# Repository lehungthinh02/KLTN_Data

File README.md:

# Bảng dữ liệu thiết kế

Thông tin chi tiết về các module được sử dụng trong thiết kế:

## Module (NB-IOT ME310G1)

| Thuộc tính    | Giá trị         |
|---------------|-----------------|
| Điện áp nguồn | 3.8V            |
| Dòng điện     | 700 mA          |
| Giao tiếp     | UART, SPI, LTE  |

## MCU (PIC32MM0256GPM064)

| Thuộc tính    | Giá trị                |
|---------------|------------------------|
| Điện áp nguồn | 2.0V đến 3.6V          |
| Dòng điện     | 0.65 μA đến 5 μA       |
| Giao tiếp     | SPI, I2C, UART, USB-OTG|

# Nguồn tài liệu

- [File 3D và danh sách bom](https://www.thingiverse.com/thing:6439737)

# Sơ đồ thiết kế

Mô tả quy trình hoạt động:

# Case of Board

Mô tả về case bảo vệ board:

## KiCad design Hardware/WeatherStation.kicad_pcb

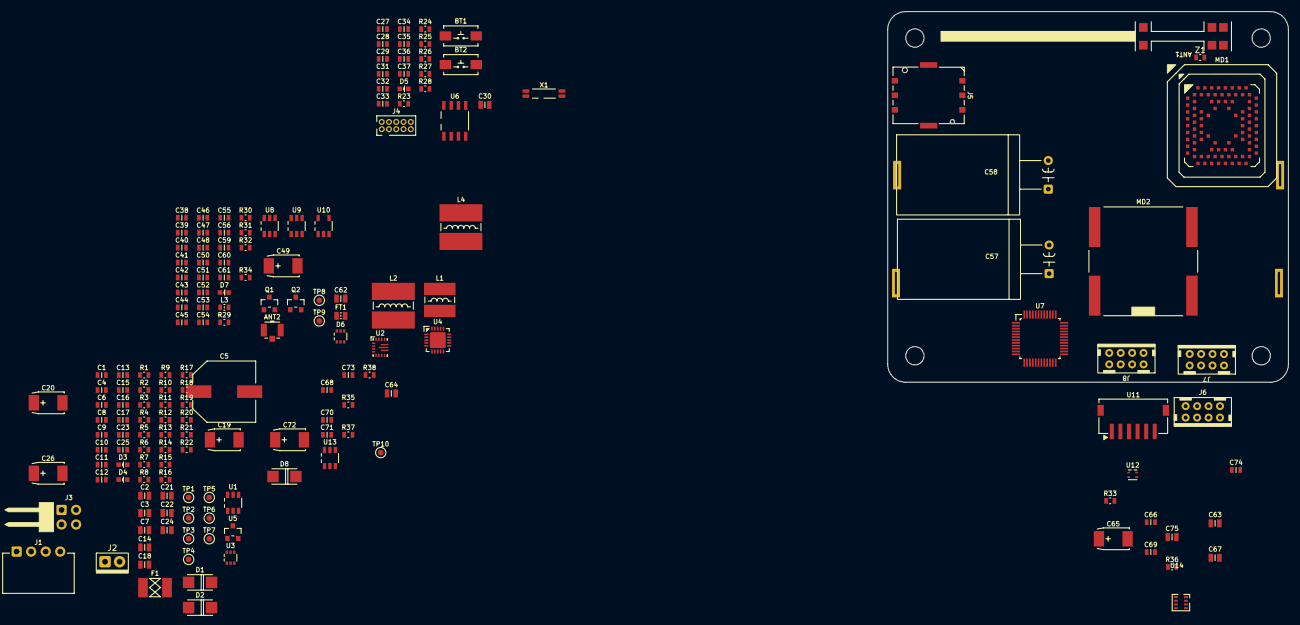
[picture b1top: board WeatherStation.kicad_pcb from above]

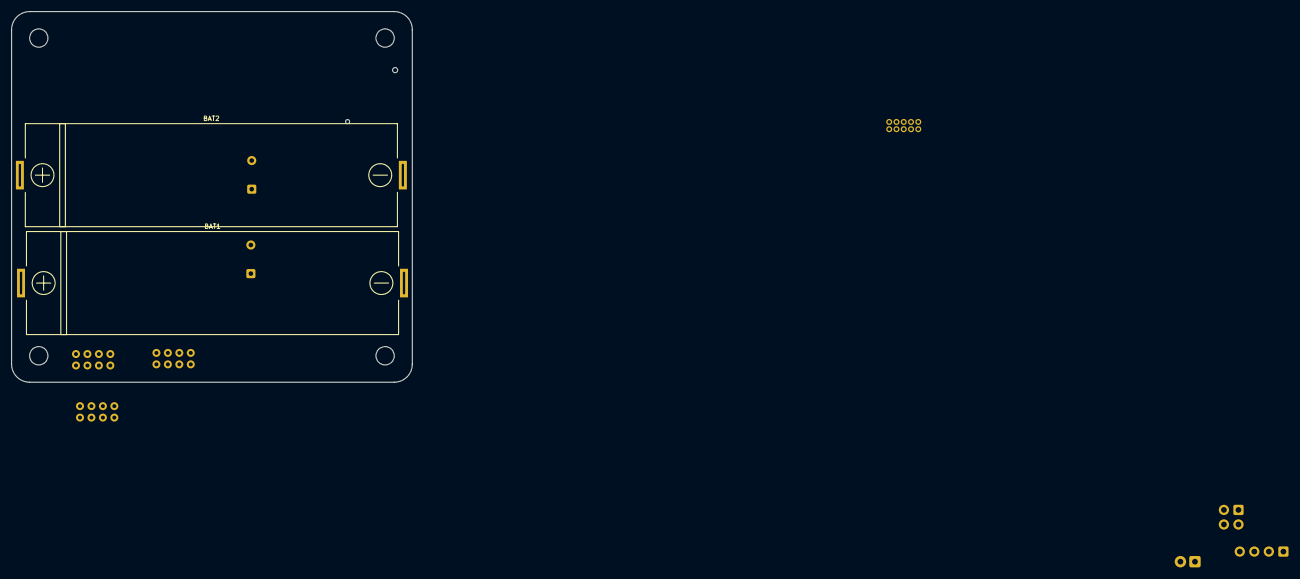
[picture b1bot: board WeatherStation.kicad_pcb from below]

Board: 2 copper layers, 70.0 x 64.7 mm, 171 parts (2 on the bottom side), 92 nets, no tracks yet.

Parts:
ANT1: 0.9-1.8GHz; AH3G.303
ANT2: UFL; U.FL
BAT1, BAT2: 3.7V/1.8Ah; BAT18650-PCBPAD
BT1: RESET; SW_SMD2_6.0x3.5
BT2: APP; SW_SMD2_6.0x3.5
C1, C6, C12, C16, C17, C25, C27, C34, C41, C42, C46, C47, C51, C61, C66, C70, C74: 100nF; CAP0603
C2, C3, C7, C14, C18, C21, C22, C24, C30, C62, C63, C64, C67, C75: 10uF; CAP0805
C4, C9, C10, C11, C13, C15, C23, C68, C69: 100pF; CAP0603
C5: 470uF; CAP_ELEC-10.3x10.3-DIA10
C8, C31, C36, C44, C50, C55, C60: 2.2uF; CAP0603
C19, C20, C26, C49, C65, C72: 220uF; CAP2312-6032
C28, C29: 8.2pF; CAP0603
C32, C33, C35, C37, C38, C39, C40, C43, C45, C48, C52, C53, C54, C56, C59, C71, C73: 22pF; CAP0603
C57, C58: 10F/2.7V; SCAP1320
D1, D2, D8: 2A/0.5VF; DO-214AC
D3: LOW BAT; LED0603
D4: CHARGE; LED0603
D5: APP; LED0603
D6: TVS-5CH; SOT363
D7: NB; LED0603
F1: 750mA/6.3V; FUSE1812
FT1: 100R@100MHz; IND0805
J1: USB; HDM-1x4x2.54-TH-RA
J2: SOLAR; PAD02_2.54TH
J3: PWR MONITOR; DIL04_2.54_MTHRA
J4: RPDBG; DIL10_1.27_MTH
J5: NANOSIM; SIM8051-6-0-14-01-A_GCT
J6, J7, J8: DIL08; HDM-2x4x2.0-TH-RA
L1: 2.2uH/3A; IND5852
L2, L4: 10uH/3A; IND7870
L3: 47nH; IND0603
MD1: NB-IoT MODULE; xE310
MD2: GPS ACTIVE ANTENNA; 1575R-A
Q1, Q2: MFET N; SOT23
R1, R6, R10, R13, R14, R15, R26, R28, R31, R32, R36: 1K; RES0603
R2, R5, R23, R24: 5.1K, 1%; RES0603
R3, R4, R9, R12, R16, R18, R20, R22, R25, R30, R35: 10K, 1%; RES0603
R7, R34: 75K, 1%; RES0603
R8: 36K, 1%; RES0603
R11: 53.6K, 1%; RES0603
R17: 100K, 1%; RES0603
R19: 680K, 1%; RES0603
R21, R27, R29: 0R; RES0603
R33: 150R; RES0603
R37, R38: 150K, 1%; RES0603
TP1: VUSB; TP1MM
TP2: VNB; TP1MM
TP3: 5V; TP1MM
TP4: 3V3; TP1MM
TP5: VBAT; TP1MM
TP6: GND; TP1MM
TP7: VDD; TP1MM
TP8: 1V8; TP1MM
TP9: VLNA; TP1MM
TP10: VBOOST; TP1MM
U1: BUCK 5V; SOT-23-6_MCHP
U2: BUCK-BOOST 3.8V; PowerVQFN15_TI
U3: IDEAL DIODE; SOT363
U4: MCP73871; VQFN20-4x4_MCHP
U5: MCP1700; SOT23
U6: SPI Memory; SOIC8_3.9_MCHP
U7: PIC32MM MCU; TQFP48-7x7_MCHP
U8, U9: LEVEL SHIFT 1-CH; SOT-23-6_MCHP
U10: LDO 3.3V/300mA; SOT-23-5_MCHP
U11: DUST SENSOR CONNECTOR; HDM-6x1.5-SMD-RA
U12: HUMI & TEMP; SHT4x
U13: BOOST 5V; SOT-23-6_MCHP
U14: DPS368
X1: 32.768kHz; SMD4-7015
Z1: 0R; RES0603

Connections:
+1V8: C46.1, C47.1, C51.1, MD1.N16 (~ONOFF/~WAKE), TP8.1, U8.6 (VCCB), U9.1 (VCCA), U9.5 (DIR)
+3.3V: C24.1, C27.1, C31.2, C33.1, C34.1, C36.1, C37.1, D3.A, J4.4 (VDD), J7.1, J8.1, R22.1, R23.2, R24.2, R25.1, R37.1, R38.1, TP4.1, U5.2 (VOUT), U6.3 (~WP), U6.7 (~HOLD), U6.8 (VDD), U7.11 (VUSB3V3), U7.18 (AVDD/VDD), U7.30 (VDD), U7.43 (VDD)
+5V: C11.1, C12.1, C14.1, C17.1, C20.+, D2.K, D4.A, R11.1, TP3.1, U3.6 (VOUT), U4.2 (VPCC), U4.4 (PROG2), U4.17 (CE), U4.18 (IN), U4.19 (IN)
/MCU/DBG_RXD: J4.3 (DBG_RX), U7.26 (TDI/AN11/C1INA/RP9/SCL2/OCM2F/RB3)
/MCU/DBG_TXD: J4.1 (DBG_TXD), U7.25 (AN4/C1INB/RP8/SDA2/OCM2E/RB2)
/MCU/NB_DN: J4.7 (USB_DM), MD1.V18 (USB_D-)
/MCU/NB_DP: J4.5 (USB_DP), MD1.U19 (USB_D+)
/MCU/NB_VBUS: J4.9 (USB_VBUS), R29.1
/MCU/PGC: J4.10 (PGC), U7.24 (PGEC1/AN3/C1INC/C2INA/RP7/OCM2D/RB1)
/MCU/PGD: J4.8 (PGD/UPDI), U7.23 (PGED1/AN2/C1IND/C2INB/C3INC/RP6/RB0)
/MCU/SCL: J7.7, J8.2, R24.1
/MCU/SDA: J7.8, J8.3, R23.1
/MCU/SOSCI: C28.1, U7.35 (SOSCI/AN7/RP10/OCM3C/RB4), X1.1 (X1)
/MCU/SOSCO: C29.1, U7.36 (SOSCO/SCLKI/RP5/PWRLCLK/OCM3D/RA4), X1.4 (X2)
/MCU/USB_DN: J1.3, U7.9 (D-/RB10)
/MCU/USB_DP: J1.2, U7.10 (D+/RB11)
/MCU/V5V_SEN: C15.1, R13.1
/MCU/VBAT_SEN: C23.1, R19.2, R20.1
/MCU/VBUS_SEN: C9.1, R6.1, U7.46 (VBUS/RB6)
/MCU/VNB_EN: R27.1, U2.1 (PS/SYNC), U2.14 (EN)
/MCU/VNB_SEN: C13.1, R10.1
/MCU/VSOLAR_SEN: C4.1, R1.1
/MCU/~BT_APP: BT2.1, C35.1, R25.2
/MCU/~MCLR: BT1.1, C32.1, J4.2 (~RESET), R22.2, U7.19 (~MCLR)
/MCU/~RNF_PULSE: C73.1, J8.8, R38.2
/MCU/~VBAT_LOW: R14.2, U4.8 (STAT1/~LDB)
/MCU/~WSP_PULSE: C71.1, J8.6, R37.2
/NB MODULE/GPS_LNA_ENA: MD1.H18 (GNSS_LNA_EN), U10.3 (EN)
/NB MODULE/RXD0: MD1.AA15 (RXD0), U9.3 (A)
/NB MODULE/SIM_CLK: C40.1, D6.3 (CH2), J5.C3 (CLK), MD1.L1 (SIM_CLK)
/NB MODULE/SIM_DAT: C38.1, D6.1 (CH1), J5.C7 (I/O), MD1.N1 (SIM_DAT)
/NB MODULE/SIM_RST: C43.1, D6.4 (CH3), J5.C2 (RST), MD1.M2 (SIM_RST)
/NB MODULE/SIM_VCC: C44.2, D6.5 (CH4), J5.C1 (VCC), MD1.P2 (SIM_VCC)
/NB MODULE/TXD0: MD1.Y16 (TXD0), R31.1
/SENSORS/SCL1: J6.7, U12.2 (SCL), U14.4 (SCK/SCL)
/SENSORS/SDA1: J6.8, U12.1 (SDA), U14.3 (SDI/SDA)
/SENSORS/VOUT: C69.1, J6.5, R36.1
/SENSORS/~LED_EN: J6.6, U11.3 (~LED_EN)
GND: ANT1.1 (GND), ANT1.3 (GND), ANT2.2 (GND), ANT2.3 (GND), BAT1.-, BAT2.-, BT1.2, BT2.2, C1.2, C2.2, C3.2, C4.2, C5.-, C6.2, C7.2, C9.2, C12.2, C13.2, C14.2, C15.2, C16.2, C17.2, C18.2, C19.-, C20.-, C21.2, C22.2, C23.2, C24.2, C25.2, C26.-, C27.2, C28.2, C29.2, C30.2, C31.1, C32.2, C33.2, C34.2, C35.2, C36.2, C37.2, C38.2, C39.2, C40.2, C41.2, C42.2, C43.2, C44.1, C45.2, C46.2, C47.2, C48.2, C49.-, C50.1, C51.2, C52.2, C54.2, C55.1, C56.2, C58.-, C59.2, C60.1, C61.2, C62.1, C64.2, C70.2, C71.2, C72.-, C73.2, D5.K, D6.2 (GND), J1.1, J2.2, J3.3, J3.4, J4.6 (GND), J5.C5 (GND), J5.S1 (SHIELD), J5.S2 (SHIELD), J7.3, J7.4, J8.4, J8.5, J8.7, MD1.A3 (GND), MD1.A7 (GND), MD1.A9 (GND), MD1.A13 (GND), MD1.A17 (GND), MD1.B4 (GND), MD1.B6 (GND), MD1.B10 (GND), MD1.B12 (GND), MD1.B14 (GND), MD1.B16 (GND), MD1.C19 (GND), MD1.D18 (GND), MD1.F8 (GND), MD1.F12 (GND), MD1.F18 (GND), MD1.G19 (GND), MD1.H6 (GND), MD1.H14 (GND), MD1.J19 (GND), MD1.K18 (GND), MD1.M18 (GND), MD1.N19 (GND), MD1.P6 (GND), MD1.P14 (GND), MD1.T8 (GND), MD1.T12 (GND), MD1.U1 (GND), MD1.V2 (GND), MD1.W19 (GND), MD1.Y2 (GND), MD1.Y4 (GND), MD2.1 (GND), MD2.2 (GND), MD2.3 (GND), MD2.4 (GND), Q1.2 (S), Q2.2 (S), R3.2, R4.2, R9.2, R12.2, R16.2, R17.2, R18.2, R20.2, R21.1, R30.2, R35.2, TP6.1, U1.1 (GND), U2.2 (PG), U2.4 (GND), U2.6 (FB2), U2.10 (PGND), U2.15 (VSEL), U3.2 (GND), U3.3 (~CE), U3.5 (ST), U4.3 (SEL), U4.9 (~TE), U4.10 (VSS), U4.11 (VSS), U4.21 (EP), U5.1 (GND), U6.4 (GND), U7.6 (VSS), U7.31 (VSS), U7.42 (VSS), U8.2 (GND), U9.2 (GND), U10.2 (GND), U13.2 (GND), X1.2 (GND1), X1.3 (GND2)
GND1: C63.2, C65.-, C66.2, C67.2, C69.2, C74.2, C75.2, J6.3, J6.4, U11.2 (LED_GND), U11.4 (GND), U11.7 (EP), U11.8 (EP), U12.4 (GND), U14.1 (GND), U14.7 (GND)
unnamed: ANT1.2 (SIG), Z1.2
unnamed: ANT2.1 (SIG), C53.2, C56.1, L3.1
unnamed: C11.2, R7.1, R11.2, R12.1, R13.2
unnamed: C21.1, J3.1, R19.1, U4.14 (VBAT), U4.15 (VBAT), U4.16 (VBAT)
unnamed: C57.-, C58.+
unnamed: C68.1, C70.1, C72.+, D8.K, J7.2, R34.1, TP10.1
unnamed: D1.A, U2.7 (VOUT), U2.8 (VOUT)
unnamed: D2.A, L2.2
unnamed: D3.K, R14.1
unnamed: D4.K, R15.2
unnamed: D5.A, R26.2
unnamed: D7.A, R32.2
unnamed: F1.1, J1.4
unnamed: MD1.A5 (CELL_ANT), Z1.1
unnamed: C48.1, C49.+, MD1.N4 (CTANK)
unnamed: C53.1, MD1.E19 (GNSS_ANT)
unnamed: MD1.R1 (PWRMON), Q2.3 (D)
unnamed: MD1.B2 (SLED), Q1.1 (G)
unnamed: C45.1, MD1.T18 (USB_VBUS), R29.2, R30.1
unnamed: C50.2, C52.1, FT1.1, MD1.AA3 (VBATT), MD1.W1 (VBATT_PA)
unnamed: D7.K, Q1.3 (D)
unnamed: R4.1, R5.1, R6.2
unnamed: C8.2, U1.6 (BS)
unnamed: R1.2, R2.1, R3.1, U1.5 (EN)
unnamed: R7.2, U1.4 (FB)
unnamed: C1.1, C5.+, J2.1, R2.2, U1.3 (IN)
unnamed: C8.1, L2.1, U1.2 (SW)
unnamed: C10.2, R8.2, R9.1, R10.2, U2.5 (FB)
unnamed: L1.2, U2.11 (L1)
unnamed: L1.1, U2.9 (L2)
unnamed: C3.1, U2.3 (VAUX)
unnamed: C6.1, C7.1, F1.2, R5.2, TP1.1, U3.1 (VIN)
unnamed: R16.1, U4.13 (PROG1)
unnamed: R17.1, U4.12 (PROG3)
unnamed: R15.1, U4.7 (STAT2)
unnamed: R18.1, U4.5 (THERM)
unnamed: R21.2, U7.17 (AVSS/VSS)
unnamed: C30.1, U7.7 (VCAP)
unnamed: R31.2, U8.4 (B)
unnamed: R28.1, U9.4 (B)
unnamed: C61.1, U10.4 (NC/BP)
unnamed: C65.+, R33.2, U11.1 (VLED)
unnamed: R36.2, U11.5 (VOUT)
unnamed: C68.2, R34.2, R35.1, U13.3 (FB)
unnamed: D8.A, L4.2, U13.1 (SW)
VBAT: BAT1.+, BAT2.+, J3.2, TP5.1
VDD: C2.1, C22.1, C25.1, C26.+, C64.1, L4.1, TP7.1, U2.12 (VIN), U2.13 (VIN), U4.1 (VBAT), U4.20 (VBAT), U5.3 (VIN), U13.5 (IN)
VDD1: C63.1, J6.2, R33.1, U11.6 (VCC)
VIO: C39.1, C41.1, C42.1, R27.2, U8.1 (VCCA), U8.5 (DIR), U9.6 (VCCB)
VLNA: C59.1, C60.2, L3.2, TP9.1, U10.5 (VOUT)
VNB: C10.1, C16.1, C18.1, C19.+, C54.1, C55.2, C57.+, C62.2, D1.K, FT1.2, R8.1, TP2.1, U10.1 (VIN)
VSEN1: C66.1, C67.1, C74.1, C75.1, J6.1, U12.3 (VDD), U14.6 (VDDIO), U14.8 (VDD)

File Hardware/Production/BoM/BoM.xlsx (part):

# | MNP | MFT | Description | Reference | Qty | Price | Sub-Price | Stock Link
1 | ZH1.5-10CM | OEM | ZH1.5 Bus Wire Female-Female Connector 6 Way, Pitch 1.5mm, Length 10cm | CB1 | 1 | 0.154 | 0.154 | https://www.thegioiic.com/day-bus-zh1-5-cai-cai-6-tiep-diem-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
2 | IDC8x2-30CM | OEM | IDC Cable Female-Female Same Direction 8-Way Connector, Pitch 2.0mm, Length 30cm | CB2 | 1 | 1.0089999999999999 | 1.0089999999999999 | https://www.thegioiic.com/day-cap-idc-cai-cai-cung-huong-8-t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
3 | IDC8x2-50CM | OEM | IDC Cable Female-Female Same Direction 8-Way Connector, Pitch 2.0mm, Length 50cm | CB3 | 1 | 1.228 | 1.228 | https://www.thegioiic.com/day-cap-idc-cai-cai-cung-huong-8-t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
4 | GP2Y1014AU | SHARP | DUST SENSOR UNIT | MD3 | 1 | 4.0789999999999997 | 4.0789999999999997 | https://www.thegioiic.com/gp2y1014au-cam-bien-bui-pm2-5
5 | SOLAR9V-2W-115x115x3 | OEM | SOLAR CELL 2W 9V 220MA 115x115x3MM | J2 | 1 | 2.851 | 2.851 | https://www.thegioiic.com/tam-nang-luong-mat-troi-2w-9v
6 | 1575R-A | AntennaHome | GPS ACTIVE ANT 19X19 IPEX CONNECTOR RF CABLE 10CM | MD2 | 1 | 1.0529999999999999 | 1.0529999999999999 | https://www.thegioiic.com/1575r-a-ang-ten-active-gps-19x19-d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
7 | AH3G.303 | AntennaHome | ANTENNA SMD 2G/3G/4G 690~2700MHz | ANT1 | 1 | 1.0960000000000001 | 1.0960000000000001 | https://www.thegioiic.com/ah3g-303-ang-ten-smd-2g-3g-4g-690-2700mhz
8 | PRT-12895 | SparkFun | BATT LITH-ION 3.7V 2.6AH 18650 | BAT1,BAT2 | 2 | 1.4039999999999999 | 2.8079999999999998 | https://www.thegioiic.com/pin-sac-18650-1800mah-3-6v-4-2v
9 | CL10B104KA8NNNC | Samsung | CAP CER 0.1UF 25V X7R 0603 | C1,C6,C12,C16,C17,C25,C27,C34,C41,C42,C46,C47,C51,C61,C66,C70,C74 | 17 | 8.3000000000000001E-3 | 0.1411 | https://www.thegioiic.com/tu-gom-0603-100nf-0-1uf-25v
10 | CL10C101JB8NNNC | Samsung | CAP CER 100PF 50V C0G/NP0 0603 | C4,C9,C10,C11,C13,C15,C23,C68,C69 | 9 | 8.3000000000000001E-3 | 7.4700000000000003E-2 | https://www.thegioiic.com/tu-gom-0603-100pf-50v
11 | CL10B225KP8NNNC | Samsung | CAP CER 2.2UF 10V X7R 0603 | C8,C31,C36,C44,C50,C55,C60 | 7 | 1.7999999999999999E-2 | 0.126 | https://www.thegioiic.com/tu-gom-0603-2-2uf-10v
12 | CL10C8R2DB8NNNC | Samsung | CAP CER 8.2PF 50V C0G/NP0 0603 | C28,C29 | 2 | 8.3000000000000001E-3 | 1.66E-2 | https://www.thegioiic.com/tu-gom-0603-8-2pf-50v
13 | CL10C220JB8NFNC | Samsung | CAP CER 22PF 50V C0G/NP0 0603 | C32,C33,C35,C37,C38,C39,C40,C43,C45,C48,C52,C53,C54,C56,C59,C71,C73 | 17 | 8.3000000000000001E-3 | 0.1411 | https://www.thegioiic.com/tu-gom-0603-22pf-50v
14 | CL21A106KOQNNNE | Samsung | CAP CER 10UF 16V X5R 0805 | C2,C3,C7,C14,C18,C21,C22,C24,C30,C62,C63,C64,C67,C75 | 14 | 1.7000000000000001E-2 | 0.23800000000000002 | https://www.thegioiic.com/tu-gom-0805-10uf-16v
15 | TAJC227K006RNJ | AVX | CAP ALUM 220UF 20% 6.3V SMD 2312 | C19,C20,C26,C49,C65,C72 | 6 | 0.24099999999999999 | 1.446 | https://www.thegioiic.com/tu-tantalum-220uf-6-3v-2312-tajc22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
16 | UUD1E471MNL1GS | Nichicon | CAP ALUM 470UF 20% 25V SMD | C5 | 1 | 8.7999999999999995E-2 | 8.7999999999999995E-2 | https://www.thegioiic.com/tu-nhom-smd-470uf-25v-10x10-5mm
17 | PH2RA-04-UA | Adam Tech | CONN HEADER R/A 2x2POS 2.54MM | J3 | 1 | 0.11 | 0.11 | https://www.thegioiic.com/hang-rao-duc-doi-2-54mm-80-chan-co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
18 | PR20B05VBDN | METZ | PIN HEADER, THR, DUAL ROW, 1.27 | J4 | 1 | 0.19700000000000001 | 0.19700000000000001 | https://www.thegioiic.com/hang-rao-duc-doi-1-27mm-80-chan-2-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
19 | SS26 | MDD | DIODE SCHOTTKY 60V 2A SMA | D1,D2,D8 | 3 | 1.7999999999999999E-2 | 5.3999999999999992E-2 | https://www.thegioiic.com/ss26-sma-diode-schottky-2a
20 | DPS368XTSA1 | Infineon | SENSOR 17.4PSIG 24BIT 8VLGA | U14 | 1 | 3.18 | 3.18 | https://www.digikey.com/en/products/detail/infineon-technolo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
21 | MF-MSMF075/24-2 | Bourns | PTC RESET FUSE 24V 750MA 1812 | F1 | 1 | 0.154 | 0.154 | https://www.thegioiic.com/mf-msmf075-24-2-cau-chi-tu-phuc-ho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
22 | XH2.54-4P-R | OEM | PIN HEADER R/A 1x4POS 2.54MM | J1 | 1 | 1.2999999999999999E-2 | 1.2999999999999999E-2 | https://www.thegioiic.com/dau-xh-2-54mm-4-chan-cong-xuyen-lo
23 | DF11-8DP-2DSA(08) | Hirose | CONN HEADER VERT 8POS 2MM | J6,J7,J8 | 3 | 7.9000000000000001E-2 | 0.23699999999999999 | https://www.thegioiic.com/cong-dc3-8-chan-2-hang-2-0mm-chan-thang
24 | S6B-ZR-SM4A-TF | JST | CONN HEADER SMD R/A 6POS 1.5MM | U11 | 1 | 3.5000000000000003E-2 | 3.5000000000000003E-2 | https://www.thegioiic.com/dau-zh-1-5mm-6-chan-dan-smd-nam-ngang
25 | HBLS1608-47NJ | HYHONGYEX | FIXED IND 47NH 380MA 700MOHM SMD 0603 | L3 | 1 | 1.7999999999999999E-2 | 1.7999999999999999E-2 | https://www.thegioiic.com/hbls1608-47nj-cuon-cam-47nh-0603-380ma
26 | BK2125HS101-T | Taiyo Yuden | FERRITE BEAD 100 OHM 0805 1LN | FT1 | 1 | 1.7999999999999999E-2 | 1.7999999999999999E-2 | https://www.thegioiic.com/bk2125hs101-t-ferrite-beads-100-ohm-0805
27 | SDE0604A-2R2M | Bourns | FIXED IND 2.2UH 4.35A 31MOHM SMD 5852 | L1 | 1 | 4.3999999999999997E-2 | 4.3999999999999997E-2 | https://www.thegioiic.com/cuon-cam-dan-smd-cd53-5852-2r2-2-2uh-3-5a
28 | SDE0805A-100M | Bourns | FIXED IND 10UH 3.2A 70 MOHM SMD | L2,L4 | 2 | 4.3999999999999997E-2 | 8.7999999999999995E-2 | https://www.thegioiic.com/cuon-cam-dan-smd-cd75-7855-100-10uh-2-3a
29 | B1931USD-20D000814U1930 | Harvatek | LED RED DIFFUSED 0603 SMD | D3 | 1 | 1.4999999999999999E-2 | 1.4999999999999999E-2 | https://www.thegioiic.com/led-do-0603-dan-smd-trong-suot-harvatek
30 | B1931NG--20D001114U1930 | Harvatek | LED GREEN DIFFUSED 0603 SMD | D4 | 1 | 1.4999999999999999E-2 | 1.4999999999999999E-2 | https://www.thegioiic.com/led-xanh-la-0603-dan-smd-trong-suo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
31 | B1911UD--20D001014U1930 | Harvatek | LED ORANGE DIFFUSED 0603 SMD | D5 | 1 | 1.4999999999999999E-2 | 1.4999999999999999E-2 | https://www.thegioiic.com/led-cam-0603-dan-smd-trong-suot-harvatek
32 | E1221NB--05D000814U1930 | Harvatek | LED BLUE DIFFUSED 0603 SMD | D7 | 1 | 1.4999999999999999E-2 | 1.4999999999999999E-2 | https://www.thegioiic.com/led-xanh-duong-0603-dan-smd-trong-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
33 | TPS630701RNMR | TI | IC REG BCK BST 5V 2A 15VQFN | U2 | 1 | 1.89 | 1.89 | https://www.digikey.com/en/products/detail/texas-instruments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
34 | AC0603JR-071KL | YAGEO | RES SMD 1K OHM 5% 1/10W 0603 | R1,R6,R10,R13,R14,R15,R26,R28,R31,R32,R36 | 11 | 1.4E-3 | 1.54E-2 | https://www.thegioiic.com/dien-tro-1-kohm-0603-5-
35 | RC0603FR-075K1L | YAGEO | RES SMD 5.1K OHM 1% 1/10W 0603 | R2,R5,R23,R24 | 4 | 2E-3 | 8.0000000000000002E-3 | https://www.digikey.com/en/products/detail/yageo/RC0603FR-07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
36 | RC0603FR-0710KL | YAGEO | RES SMD 10K OHM 1% 1/10W 0603 | R3,R4,R9,R12,R16,R18,R20,R22,R25,R30,R35 | 11 | 2E-3 | 2.1999999999999999E-2 | https://www.thegioiic.com/dien-tro-10-kohm-0603-1-
37 | AC0603FR-0775KL | YAGEO | RES SMD 75K OHM 1% 1/10W 0603 | R7,R34 | 2 | 2E-3 | 4.0000000000000001E-3 | https://www.thegioiic.com/dien-tro-75-kohm-0603-1-
38 | RT0603FRE0736KL | YAGEO | RES SMD 36K OHM 1% 1/10W 0603 | R8 | 1 | 2E-3 | 2E-3 | https://www.digikey.com/en/products/detail/yageo/RT0603FRE07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
39 | RC0603FR-0753K6L | YAGEO | RES SMD 53.6K OHM 1% 1/10W 0603 | R11 | 1 | 2E-3 | 2E-3 | https://www.thegioiic.com/dien-tro-53-6-kohm-0603-1-
40 | RC0603FR-07100KL | YAGEO | RES SMD 100K OHM 1% 1/10W 0603 | R17 | 1 | 2E-3 | 2E-3 | https://www.thegioiic.com/dien-tro-100-kohm-0603-1-
41 | RC0603FR-07680KL | YAGEO | RES SMD 680K OHM 1% 1/10W 0603 | R19 | 1 | 2E-3 | 2E-3 | https://www.thegioiic.com/dien-tro-680-kohm-0603-1-
42 | RC0603JR-070RL | YAGEO | RES SMD 0 OHM JUMPER 1/10W 0603 | R21,R27,R29,Z1 | 4 | 2E-3 | 8.0000000000000002E-3 | https://www.thegioiic.com/dien-tro-0-ohm-0603-1-
43 | RC0603JR-07150RL | YAGEO | RES SMD 150 OHM 5% 1/10W 0603 | R33 | 1 | 1.4E-3 | 1.4E-3 | https://www.thegioiic.com/dien-tro-150-ohm-0603-5-
44 | RC0603FR-13150KL | YAGEO | RES SMD 150K OHM 1% 1/10W 0603 | R37,R38 | 2 | 2E-3 | 4.0000000000000001E-3 | https://www.thegioiic.com/dien-tro-150-kohm-0603-1-
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
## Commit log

2024-03-17 Update README.md
    check readME
2024-03-17 Update README.md
    check1
2024-03-17 Update README.md
    check11
2024-03-17 Update README.md
    check
2024-03-17 Update README.md check12
2024-03-17 Điện áp nguồn
    dữ liệu từ datasheet cảm biến
2024-03-17 CHECK
    check1
2024-03-17 COMMITDATA.md
    bảng dữ liệu chuẩn
2024-03-17 CHECK1
    thêm nguồn tài liệu
2024-03-18 UPDATE
    update
2024-03-18 check
    check
2024-03-18 CHECK
    CHECKa
2024-03-22 POWER1
    POWER1
2024-03-22 CHECKV1.0
    CHECK1.0
2024-03-22 Flowchart update
    update
2024-04-03 FIX
    fix
2024-04-03 UPDATE_FLOWCHART
    update
2024-04-05 Fix_floatchart
    fix
2024-04-05 fix_flowchart
    FIX
2024-04-05 Case
    case
2024-04-05 Update read me
    Update read me
2024-04-05 Fix read me
    Fix read me
2024-04-09 UPDATE HARDWARE
    UPDATE
2024-04-11 UPDATE outline
    update outline
2024-04-11 update outline
    outline
2024-04-12 UPDATE _FOOTPRINT
    UPDATE
2024-04-15 Update check BoM
    update BoM
2024-04-15 Update readme
    Update
